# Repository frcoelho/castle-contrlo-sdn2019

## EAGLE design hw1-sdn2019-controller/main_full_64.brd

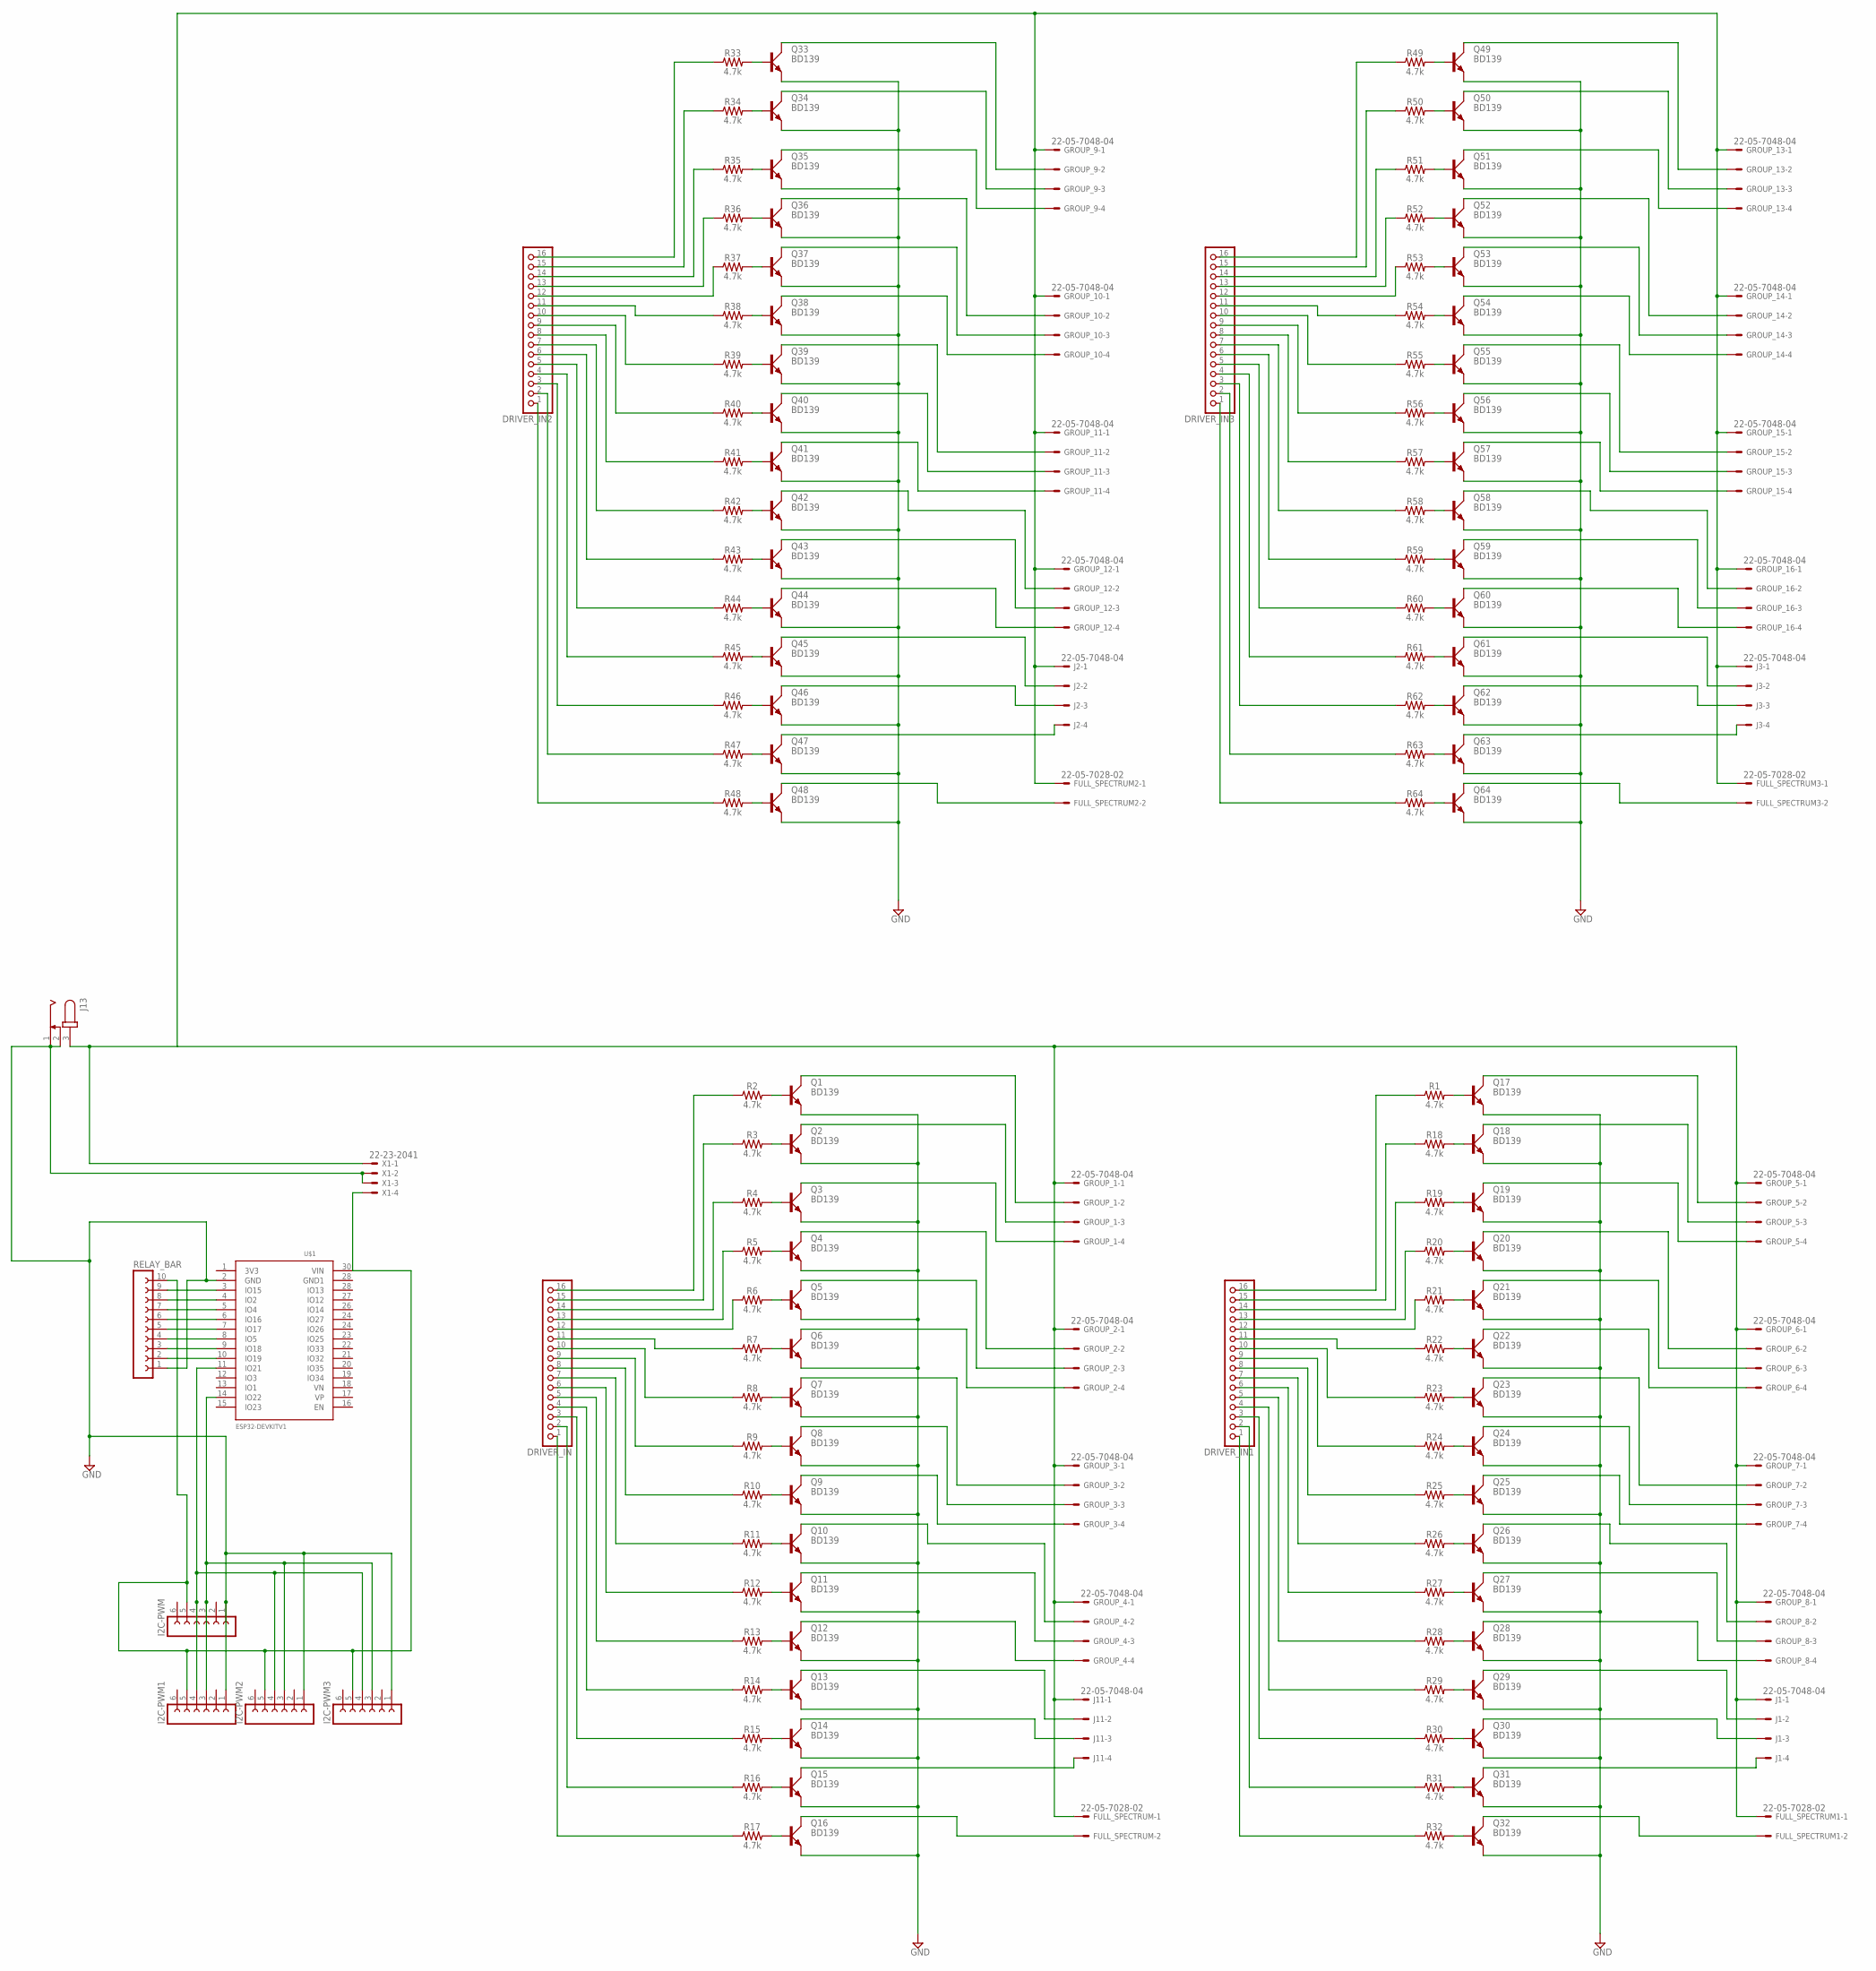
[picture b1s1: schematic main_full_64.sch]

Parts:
DRIVER_IN, DRIVER_IN1, DRIVER_IN2, DRIVER_IN3: PINHD-1X16/90; 1X16/90
FULL_SPECTRUM, FULL_SPECTRUM1, FULL_SPECTRUM2, FULL_SPECTRUM3: 22-05-7028-02; 7395-02
GROUP_1, GROUP_2, GROUP_3, GROUP_4, GROUP_5, GROUP_6, GROUP_7, GROUP_8, GROUP_9, GROUP_10, GROUP_11, GROUP_12, GROUP_13, GROUP_14, GROUP_15, GROUP_16: 22-05-7048-04; 7395-04
I2C-PWM, I2C-PWM1, I2C-PWM2, I2C-PWM3: FE06W
J1, J2, J3, J11: 22-05-7048-04; 7395-04
J13: JACK-PLUG0; SPC4077
Q1, Q2, Q3, Q4, Q5, Q6, Q7, Q8, Q9, Q10, Q11, Q12, Q13, Q14, Q15, Q16, Q17, Q18, Q19, Q20, Q21, Q22, Q23, Q24, Q25, Q26, Q27, Q28, Q29, Q30, Q31, Q32, Q33, Q34, Q35, Q36, Q37, Q38, Q39, Q40, Q41, Q42, Q43, Q44, Q45, Q46, Q47, Q48, Q49, Q50, Q51, Q52, Q53, Q54, Q55, Q56, Q57, Q58, Q59, Q60, Q61, Q62, Q63, Q64: BD139; TO126AV
R1, R2, R3, R4, R5, R6, R7, R8, R9, R10, R11, R12, R13, R14, R15, R16, R17, R18, R19, R20, R21, R22, R23, R24, R25, R26, R27, R28, R29, R30, R31, R32, R33, R34, R35, R36, R37, R38, R39, R40, R41, R42, R43, R44, R45, R46, R47, R48, R49, R50, R51, R52, R53, R54, R55, R56, R57, R58, R59, R60, R61, R62, R63, R64: 4.7k; 0603
RELAY_BAR: FE10W
U$1: ESP32DEVKITV1; ESP32-DEVKITV1
X1: 22-23-2041

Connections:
GND: I2C-PWM.1, I2C-PWM1.1, I2C-PWM2.1, I2C-PWM3.1, J13.1, J13.2, Q1.E, Q2.E, Q3.E, Q4.E, Q5.E, Q6.E, Q7.E, Q8.E, Q9.E, Q10.E, Q11.E, Q12.E, Q13.E, Q14.E, Q15.E, Q16.E, Q17.E, Q18.E, Q19.E, Q20.E, Q21.E, Q22.E, Q23.E, Q24.E, Q25.E, Q26.E, Q27.E, Q28.E, Q29.E, Q30.E, Q31.E, Q32.E, Q33.E, Q34.E, Q35.E, Q36.E, Q37.E, Q38.E, Q39.E, Q40.E, Q41.E, Q42.E, Q43.E, Q44.E, Q45.E, Q46.E, Q47.E, Q48.E, Q49.E, Q50.E, Q51.E, Q52.E, Q53.E, Q54.E, Q55.E, Q56.E, Q57.E, Q58.E, Q59.E, Q60.E, Q61.E, Q62.E, Q63.E, Q64.E, RELAY_BAR.1, U$1.2 (GND), X1.2, X1.3
unnamed: FULL_SPECTRUM.1, FULL_SPECTRUM1.1, FULL_SPECTRUM2.1, FULL_SPECTRUM3.1, GROUP_1.1, GROUP_2.1, GROUP_3.1, GROUP_4.1, GROUP_5.1, GROUP_6.1, GROUP_7.1, GROUP_8.1, GROUP_9.1, GROUP_10.1, GROUP_11.1, GROUP_12.1, GROUP_13.1, GROUP_14.1, GROUP_15.1, GROUP_16.1, J1.1, J2.1, J3.1, J11.1, J13.3, X1.1
unnamed: Q1.B, R2.2
unnamed: Q2.B, R3.2
unnamed: Q3.B, R4.2
unnamed: Q4.B, R5.2
unnamed: Q5.B, R6.2
unnamed: Q6.B, R7.2
unnamed: Q7.B, R8.2
unnamed: Q8.B, R9.2
unnamed: Q9.B, R10.2
unnamed: Q10.B, R11.2
unnamed: Q11.B, R12.2
unnamed: Q12.B, R13.2
unnamed: Q13.B, R14.2
unnamed: Q14.B, R15.2
unnamed: Q15.B, R16.2
unnamed: Q16.B, R17.2
unnamed: DRIVER_IN.1, R17.1
unnamed: DRIVER_IN.2, R16.1
unnamed: DRIVER_IN.3, R15.1
unnamed: DRIVER_IN.4, R14.1
unnamed: DRIVER_IN.5, R13.1
unnamed: DRIVER_IN.6, R12.1
unnamed: DRIVER_IN.7, R11.1
unnamed: DRIVER_IN.8, R10.1
unnamed: DRIVER_IN.9, R9.1
unnamed: DRIVER_IN.10, R8.1
unnamed: DRIVER_IN.11, R7.1
unnamed: DRIVER_IN.12, R6.1
unnamed: DRIVER_IN.13, R5.1
unnamed: DRIVER_IN.14, R4.1
unnamed: DRIVER_IN.15, R3.1
unnamed: DRIVER_IN.16, R2.1
unnamed: RELAY_BAR.9, U$1.3 (IO15)
unnamed: RELAY_BAR.8, U$1.4 (IO2)
unnamed: RELAY_BAR.7, U$1.5 (IO4)
unnamed: RELAY_BAR.6, U$1.6 (IO16)
unnamed: RELAY_BAR.5, U$1.7 (IO17)
unnamed: RELAY_BAR.4, U$1.8 (IO5)
unnamed: RELAY_BAR.3, U$1.9 (IO18)
unnamed: RELAY_BAR.2, U$1.10 (IO19)
unnamed: Q17.B, R1.2
unnamed: Q18.B, R18.2
unnamed: Q19.B, R19.2
unnamed: Q20.B, R20.2
unnamed: Q21.B, R21.2
unnamed: GROUP_1.2, Q1.C
unnamed: GROUP_1.3, Q2.C
unnamed: GROUP_1.4, Q3.C
unnamed: GROUP_2.2, Q4.C
unnamed: GROUP_2.3, Q5.C
unnamed: GROUP_2.4, Q6.C
unnamed: GROUP_3.2, Q7.C
unnamed: GROUP_3.3, Q8.C
unnamed: GROUP_3.4, Q9.C
unnamed: GROUP_4.2, Q10.C
unnamed: GROUP_4.3, Q11.C
unnamed: GROUP_4.4, Q12.C
unnamed: Q22.B, R22.2
unnamed: J11.2, Q13.C
unnamed: J11.3, Q14.C
unnamed: J11.4, Q15.C
unnamed: FULL_SPECTRUM.2, Q16.C
unnamed: Q23.B, R23.2
unnamed: Q24.B, R24.2
unnamed: Q25.B, R25.2
unnamed: Q26.B, R26.2
unnamed: Q27.B, R27.2
unnamed: Q28.B, R28.2
unnamed: Q29.B, R29.2
unnamed: Q30.B, R30.2
unnamed: Q31.B, R31.2
unnamed: Q32.B, R32.2
unnamed: DRIVER_IN1.1, R32.1
unnamed: DRIVER_IN1.2, R31.1
unnamed: DRIVER_IN1.3, R30.1
unnamed: DRIVER_IN1.4, R29.1
unnamed: DRIVER_IN1.5, R28.1
unnamed: DRIVER_IN1.6, R27.1
unnamed: DRIVER_IN1.7, R26.1
unnamed: DRIVER_IN1.8, R25.1
unnamed: DRIVER_IN1.9, R24.1
unnamed: DRIVER_IN1.10, R23.1
unnamed: DRIVER_IN1.11, R22.1
unnamed: DRIVER_IN1.12, R21.1
unnamed: DRIVER_IN1.13, R20.1
unnamed: DRIVER_IN1.14, R19.1
unnamed: DRIVER_IN1.15, R18.1
unnamed: DRIVER_IN1.16, R1.1
unnamed: GROUP_5.2, Q17.C
unnamed: GROUP_5.3, Q18.C
unnamed: GROUP_5.4, Q19.C
unnamed: GROUP_6.2, Q20.C
unnamed: GROUP_6.3, Q21.C
unnamed: GROUP_6.4, Q22.C
unnamed: GROUP_7.2, Q23.C
unnamed: GROUP_7.3, Q24.C
unnamed: GROUP_7.4, Q25.C
unnamed: GROUP_8.2, Q26.C
unnamed: GROUP_8.3, Q27.C
unnamed: GROUP_8.4, Q28.C
unnamed: J1.2, Q29.C
unnamed: J1.3, Q30.C
unnamed: J1.4, Q31.C
unnamed: FULL_SPECTRUM1.2, Q32.C
unnamed: Q33.B, R33.2
unnamed: Q34.B, R34.2
unnamed: Q35.B, R35.2
unnamed: Q36.B, R36.2
unnamed: Q37.B, R37.2
unnamed: Q38.B, R38.2
unnamed: Q39.B, R39.2
unnamed: Q40.B, R40.2
unnamed: Q41.B, R41.2
unnamed: Q42.B, R42.2
unnamed: Q43.B, R43.2
unnamed: Q44.B, R44.2
unnamed: Q45.B, R45.2
unnamed: Q46.B, R46.2
unnamed: Q47.B, R47.2
unnamed: Q48.B, R48.2
unnamed: DRIVER_IN2.1, R48.1
unnamed: DRIVER_IN2.2, R47.1
unnamed: DRIVER_IN2.3, R46.1
unnamed: DRIVER_IN2.4, R45.1
unnamed: DRIVER_IN2.5, R44.1
unnamed: DRIVER_IN2.6, R43.1
unnamed: DRIVER_IN2.7, R42.1
unnamed: DRIVER_IN2.8, R41.1
unnamed: DRIVER_IN2.9, R40.1
unnamed: DRIVER_IN2.10, R39.1
unnamed: DRIVER_IN2.11, R38.1
unnamed: DRIVER_IN2.12, R37.1
unnamed: DRIVER_IN2.13, R36.1
unnamed: DRIVER_IN2.14, R35.1
unnamed: DRIVER_IN2.15, R34.1
unnamed: DRIVER_IN2.16, R33.1
unnamed: GROUP_9.2, Q33.C
unnamed: GROUP_9.3, Q34.C
unnamed: GROUP_9.4, Q35.C
unnamed: GROUP_10.2, Q36.C
unnamed: GROUP_10.3, Q37.C
unnamed: GROUP_10.4, Q38.C
unnamed: GROUP_11.2, Q39.C
unnamed: GROUP_11.3, Q40.C
unnamed: GROUP_11.4, Q41.C
unnamed: GROUP_12.2, Q42.C
unnamed: GROUP_12.3, Q43.C
unnamed: GROUP_12.4, Q44.C
unnamed: J2.2, Q45.C
unnamed: J2.3, Q46.C
unnamed: J2.4, Q47.C
unnamed: FULL_SPECTRUM2.2, Q48.C
unnamed: Q49.B, R49.2
unnamed: Q50.B, R50.2
unnamed: Q51.B, R51.2
unnamed: Q52.B, R52.2
unnamed: Q53.B, R53.2
unnamed: Q54.B, R54.2
unnamed: Q55.B, R55.2
unnamed: Q56.B, R56.2
unnamed: Q57.B, R57.2
unnamed: Q58.B, R58.2
unnamed: Q59.B, R59.2
unnamed: Q60.B, R60.2
unnamed: Q61.B, R61.2
unnamed: Q62.B, R62.2
unnamed: Q63.B, R63.2
unnamed: Q64.B, R64.2
unnamed: DRIVER_IN3.1, R64.1
unnamed: DRIVER_IN3.2, R63.1
unnamed: DRIVER_IN3.3, R62.1
unnamed: DRIVER_IN3.4, R61.1
unnamed: DRIVER_IN3.5, R60.1
unnamed: DRIVER_IN3.6, R59.1
unnamed: DRIVER_IN3.7, R58.1
unnamed: DRIVER_IN3.8, R57.1
unnamed: DRIVER_IN3.9, R56.1
unnamed: DRIVER_IN3.10, R55.1
unnamed: DRIVER_IN3.11, R54.1
unnamed: DRIVER_IN3.12, R53.1
unnamed: DRIVER_IN3.13, R52.1
unnamed: DRIVER_IN3.14, R51.1
unnamed: DRIVER_IN3.15, R50.1
unnamed: DRIVER_IN3.16, R49.1
unnamed: GROUP_13.2, Q49.C
unnamed: GROUP_13.3, Q50.C
unnamed: GROUP_13.4, Q51.C
unnamed: GROUP_14.2, Q52.C
unnamed: GROUP_14.3, Q53.C
unnamed: GROUP_14.4, Q54.C
unnamed: GROUP_15.2, Q55.C
unnamed: GROUP_15.3, Q56.C
unnamed: GROUP_15.4, Q57.C
unnamed: GROUP_16.2, Q58.C
unnamed: GROUP_16.3, Q59.C
unnamed: GROUP_16.4, Q60.C
unnamed: J3.2, Q61.C
unnamed: J3.3, Q62.C
unnamed: J3.4, Q63.C
unnamed: FULL_SPECTRUM3.2, Q64.C
unnamed: I2C-PWM.4, I2C-PWM1.4, I2C-PWM2.4, I2C-PWM3.4, U$1.11 (IO21)
unnamed: I2C-PWM.3, I2C-PWM1.3, I2C-PWM2.3, I2C-PWM3.3, U$1.14 (IO22)
unnamed: I2C-PWM.5, I2C-PWM1.5, I2C-PWM2.5, I2C-PWM3.5, RELAY_BAR.10, U$1.30 (VIN), X1.4

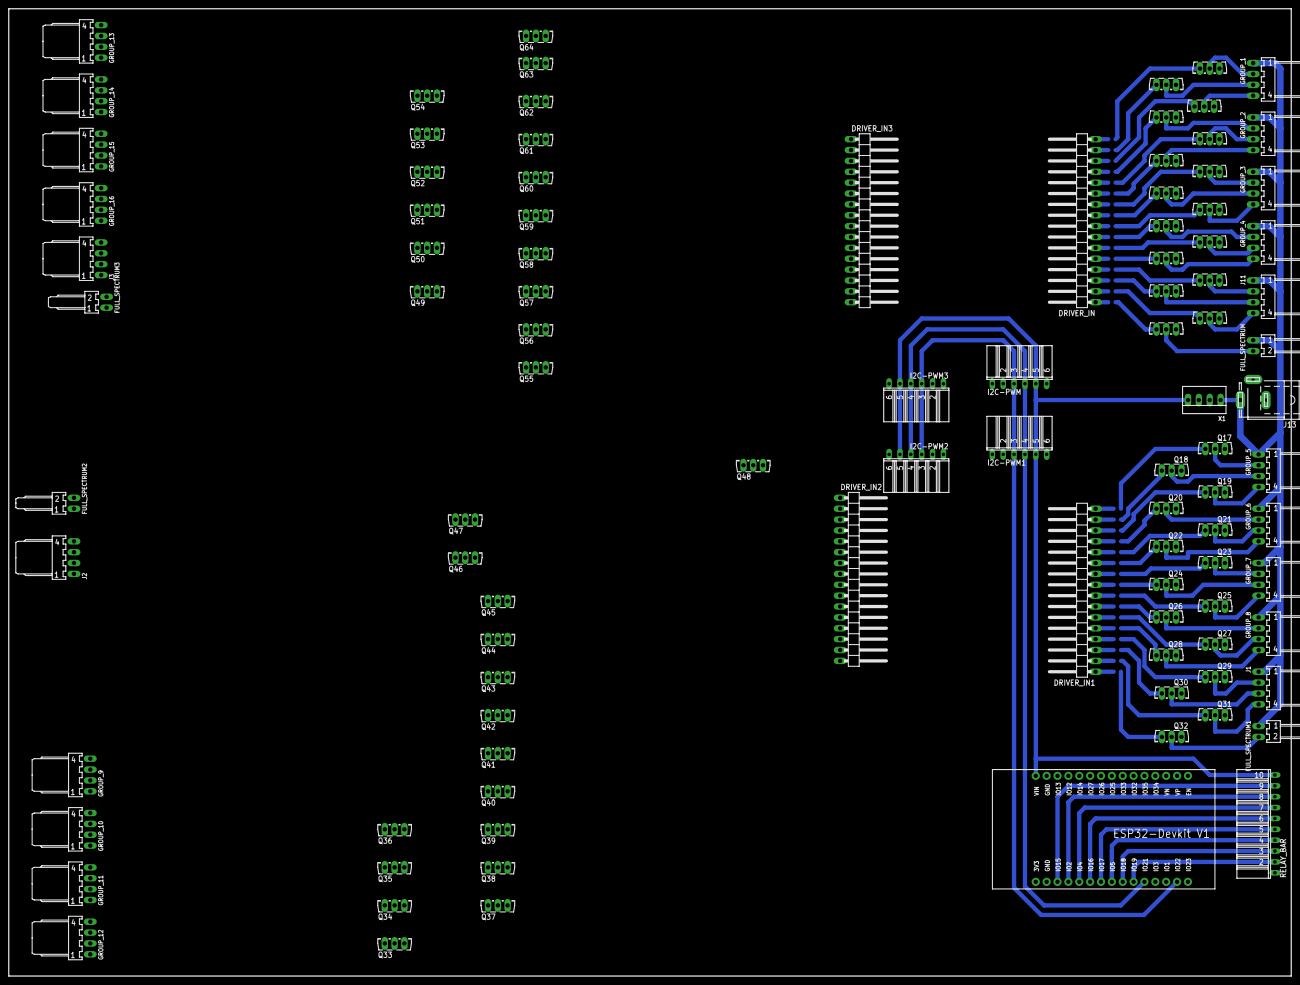
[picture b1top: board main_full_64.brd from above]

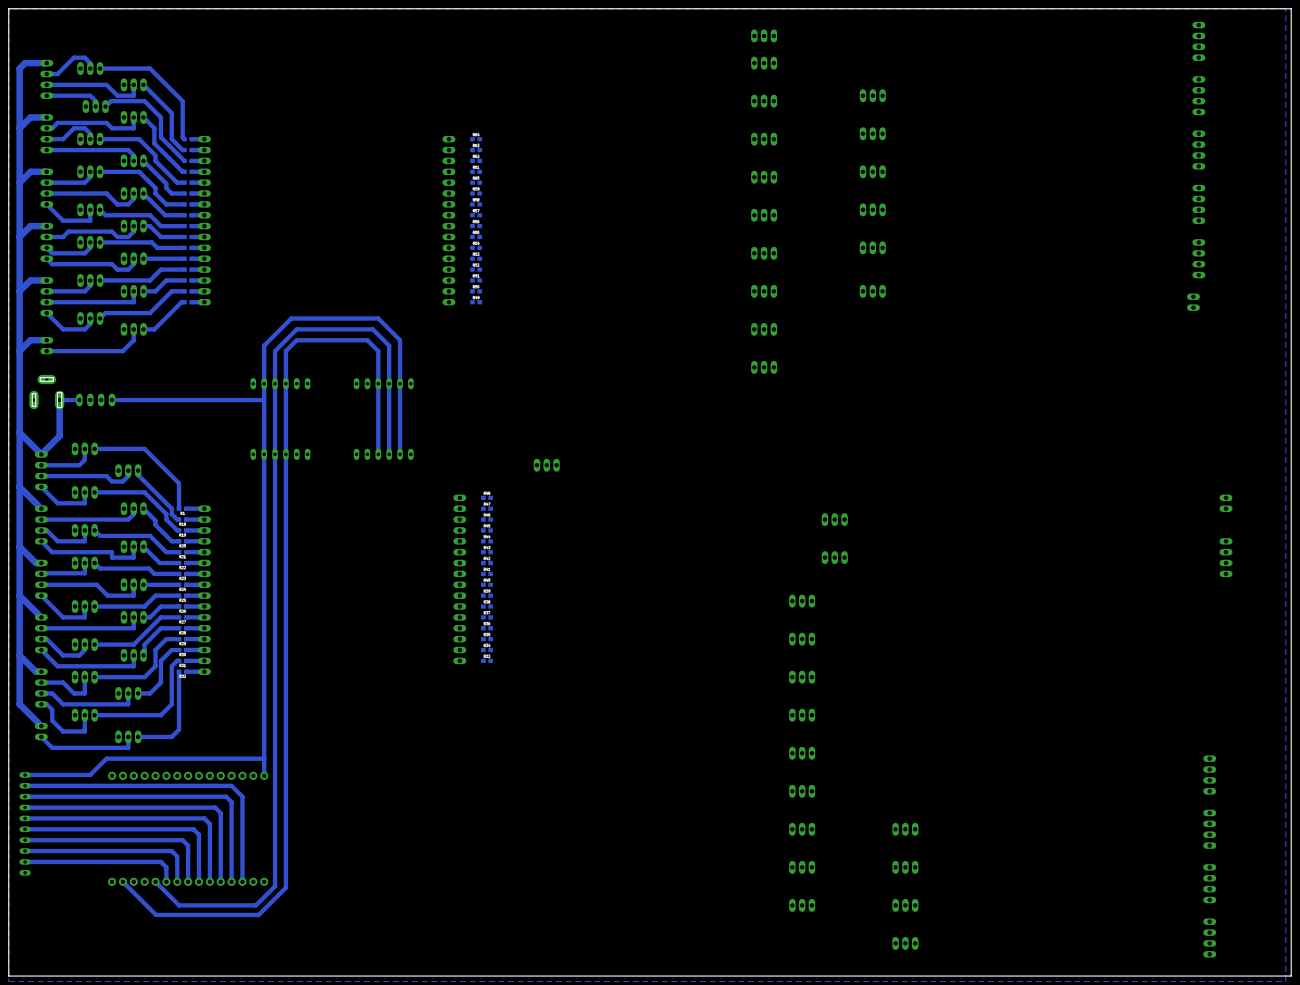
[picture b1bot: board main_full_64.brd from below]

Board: 2 copper layers, 299.7 x 226.1 mm, 164 parts (64 on the bottom side), 205 nets.

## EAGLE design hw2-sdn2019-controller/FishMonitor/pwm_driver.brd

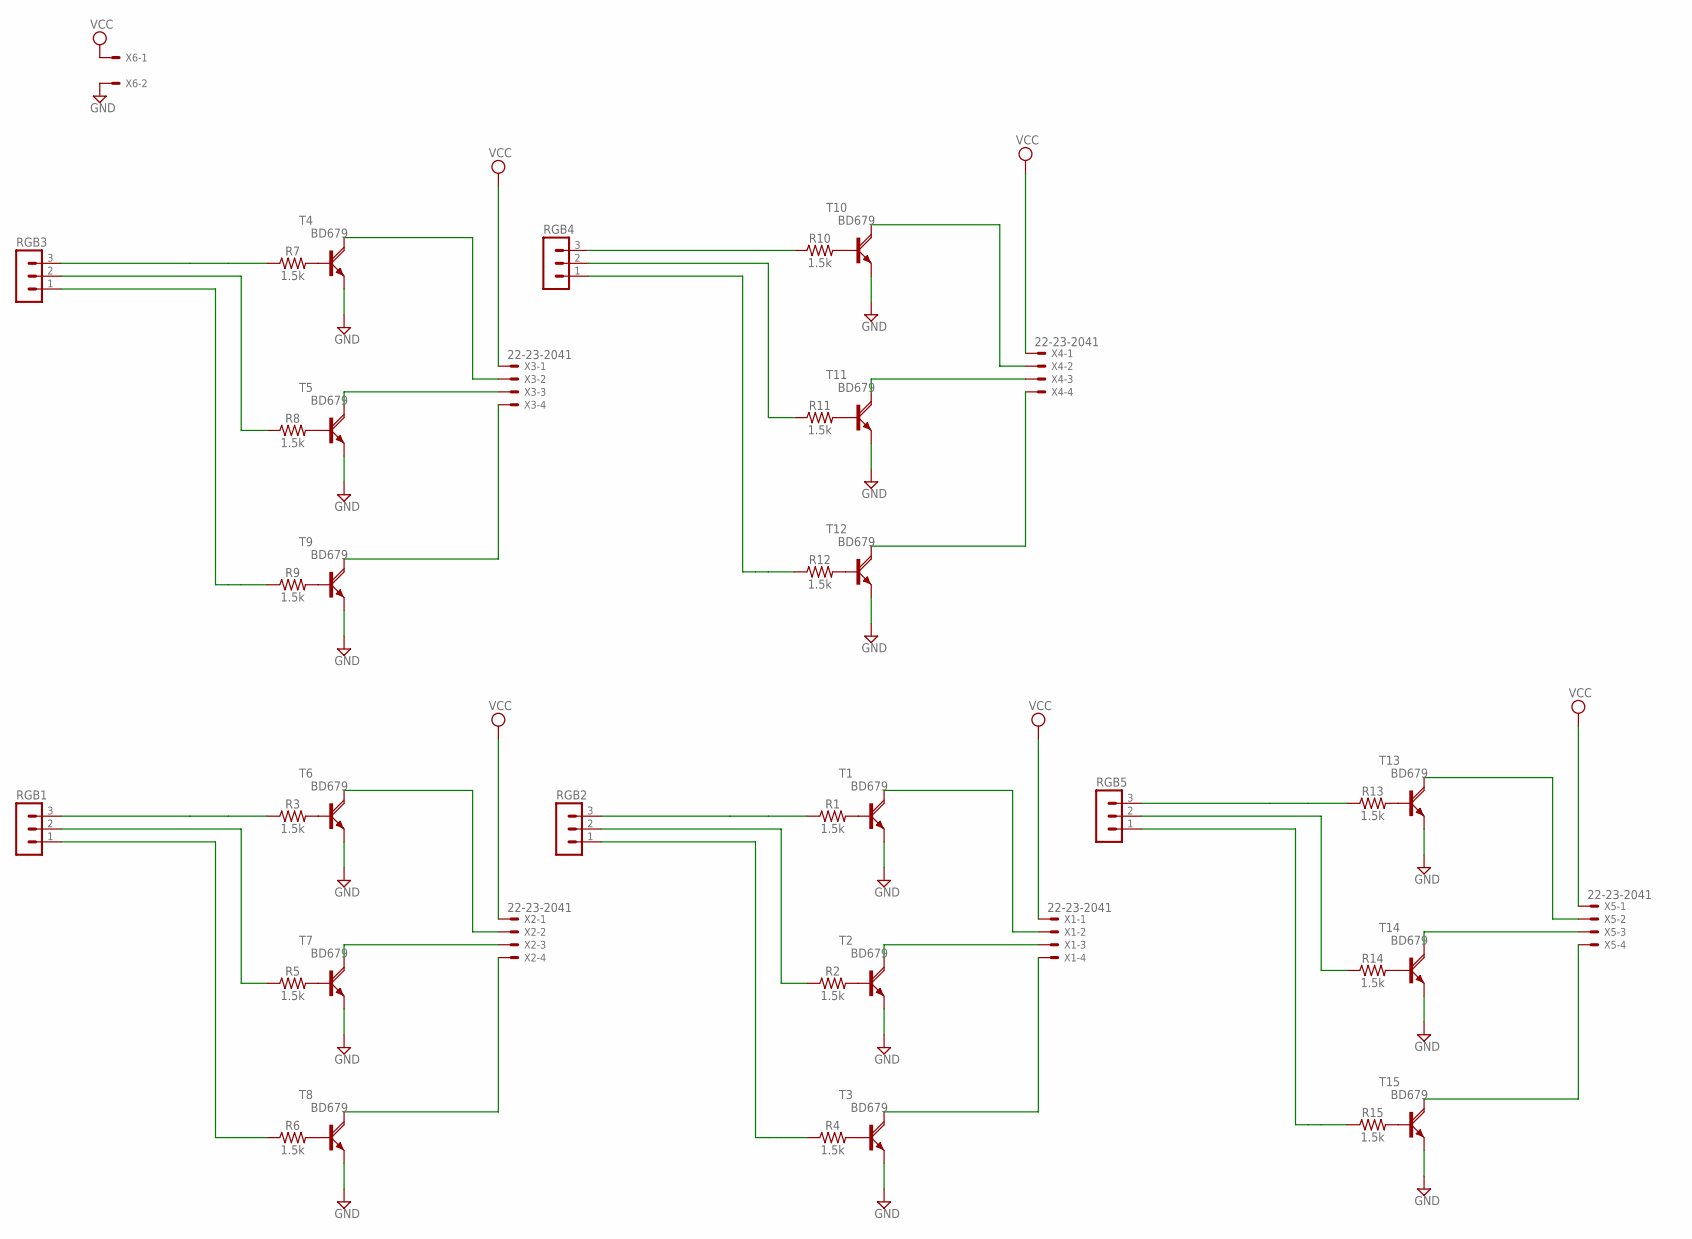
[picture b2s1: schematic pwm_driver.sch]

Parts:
R1, R2, R3, R4, R5, R6, R7, R8, R9, R10, R11, R12, R13, R14, R15: 1.5k; 0603
RGB1, RGB2, RGB3, RGB4, RGB5: MA03-1
T1, T2, T3, T4, T5, T6, T7, T8, T9, T10, T11, T12, T13, T14, T15: BD679; TO126AV
X1, X2, X3, X4, X5: 22-23-2041
X6: KK-156-2

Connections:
GND: T1.E, T2.E, T3.E, T4.E, T5.E, T6.E, T7.E, T8.E, T9.E, T10.E, T11.E, T12.E, T13.E, T14.E, T15.E, X6.2
unnamed: R3.2, T6.B
unnamed: R5.2, T7.B
unnamed: R6.2, T8.B
unnamed: R1.1, RGB2.3
unnamed: R2.1, RGB2.2
unnamed: R4.1, RGB2.1
unnamed: T1.C, X1.2
unnamed: T2.C, X1.3
unnamed: T3.C, X1.4
unnamed: R1.2, T1.B
unnamed: R2.2, T2.B
unnamed: R4.2, T3.B
unnamed: R7.1, RGB3.3
unnamed: R8.1, RGB3.2
unnamed: R9.1, RGB3.1
unnamed: R3.1, RGB1.3
unnamed: R5.1, RGB1.2
unnamed: R6.1, RGB1.1
unnamed: T4.C, X3.2
unnamed: T5.C, X3.3
unnamed: T6.C, X2.2
unnamed: T7.C, X2.3
unnamed: T8.C, X2.4
unnamed: T9.C, X3.4
unnamed: R7.2, T4.B
unnamed: R8.2, T5.B
unnamed: R9.2, T9.B
unnamed: R10.1, RGB4.3
unnamed: R11.1, RGB4.2
unnamed: R12.1, RGB4.1
unnamed: T10.C, X4.2
unnamed: T11.C, X4.3
unnamed: T12.C, X4.4
unnamed: R10.2, T10.B
unnamed: R11.2, T11.B
unnamed: R12.2, T12.B
unnamed: R13.1, RGB5.3
unnamed: R14.1, RGB5.2
unnamed: R15.1, RGB5.1
unnamed: T13.C, X5.2
unnamed: T14.C, X5.3
unnamed: T15.C, X5.4
unnamed: R13.2, T13.B
unnamed: R14.2, T14.B
unnamed: R15.2, T15.B
VCC: X1.1, X2.1, X3.1, X4.1, X5.1, X6.1

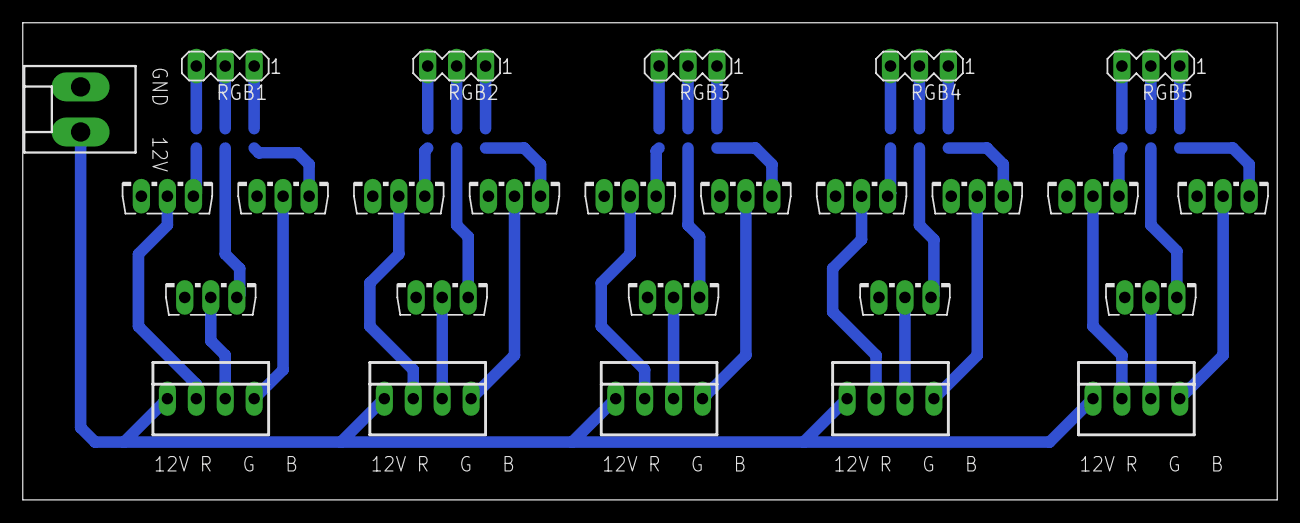
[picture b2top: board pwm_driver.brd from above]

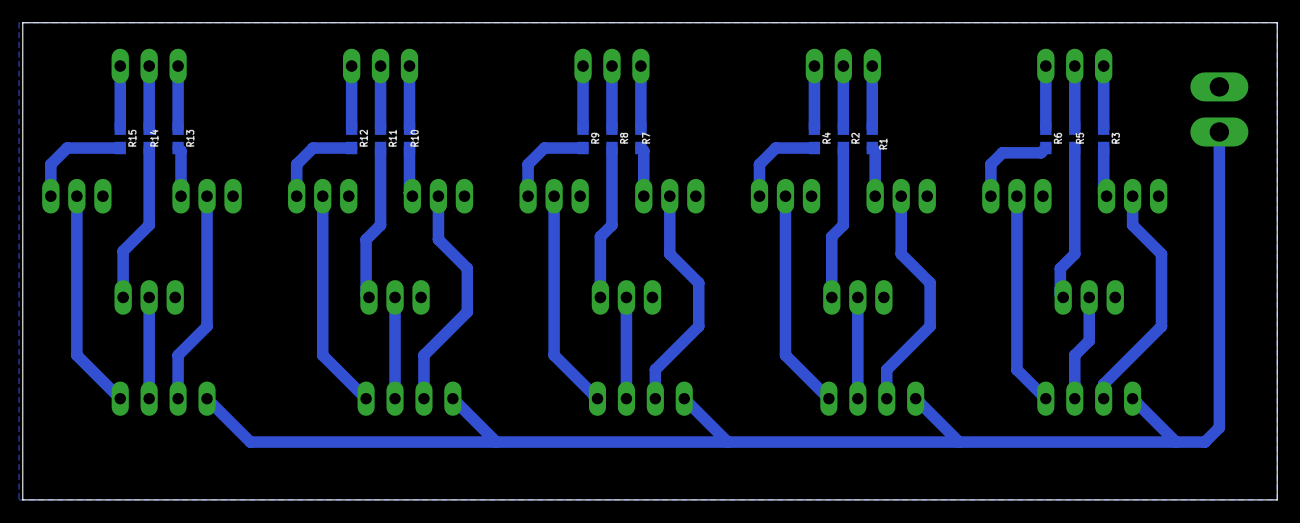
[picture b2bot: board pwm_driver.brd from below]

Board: 2 copper layers, 110.2 x 41.9 mm, 41 parts (15 on the bottom side), 47 nets.

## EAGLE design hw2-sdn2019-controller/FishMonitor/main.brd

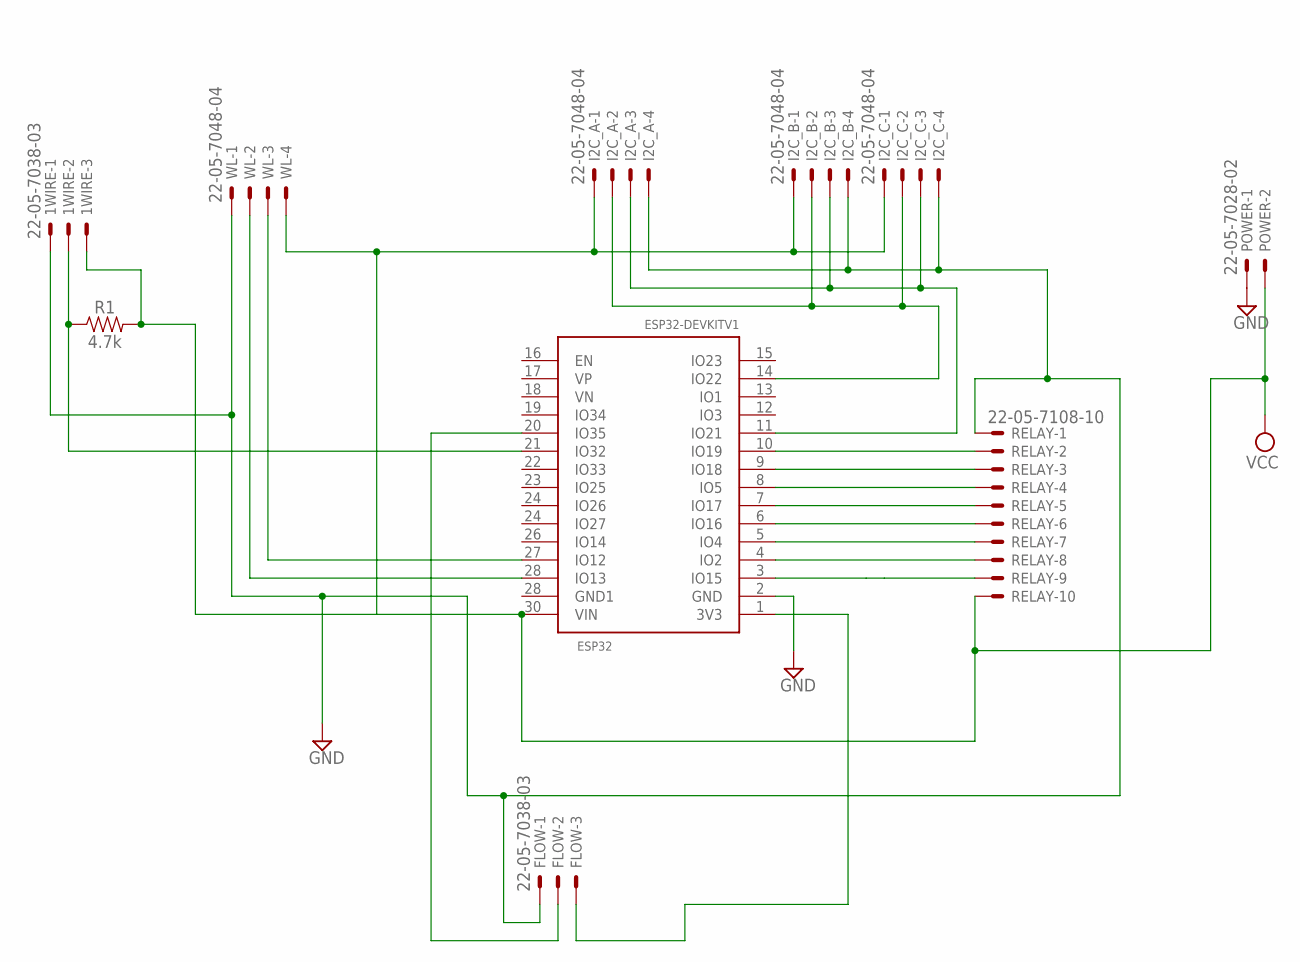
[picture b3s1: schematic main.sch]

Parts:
1WIRE: 22-05-7038-03; 7395-03
ESP32: ESP32DEVKITV1; ESP32-DEVKITV1
FLOW: 22-05-7038-03; 7395-03
I2C_A, I2C_B, I2C_C: 22-05-7048-04; 7395-04
POWER: 22-05-7028-02; 7395-02
R1: 4.7k; 0603
RELAY: 22-05-7108-10; 7395-10
WL: 22-05-7048-04; 7395-04

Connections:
GND: 1WIRE.1, ESP32.2 (GND), FLOW.1, I2C_A.4, I2C_B.4, I2C_C.4, POWER.1, RELAY.1, WL.1
unnamed: ESP32.3 (IO15), RELAY.9
unnamed: ESP32.4 (IO2), RELAY.8
unnamed: ESP32.5 (IO4), RELAY.7
unnamed: ESP32.6 (IO16), RELAY.6
unnamed: ESP32.7 (IO17), RELAY.5
unnamed: ESP32.8 (IO5), RELAY.4
unnamed: ESP32.9 (IO18), RELAY.3
unnamed: ESP32.10 (IO19), RELAY.2
unnamed: ESP32.27 (IO12), WL.3
unnamed: ESP32.28 (IO13), WL.2
unnamed: ESP32.11 (IO21), I2C_A.3, I2C_B.3, I2C_C.3
unnamed: ESP32.14 (IO22), I2C_A.2, I2C_B.2, I2C_C.2
unnamed: 1WIRE.2, ESP32.21 (IO32), R1.1
unnamed: ESP32.20 (IO35), FLOW.2
unnamed: ESP32.1 (3V3), FLOW.3
VCC: 1WIRE.3, ESP32.30 (VIN), I2C_A.1, I2C_B.1, I2C_C.1, POWER.2, R1.2, RELAY.10, WL.4

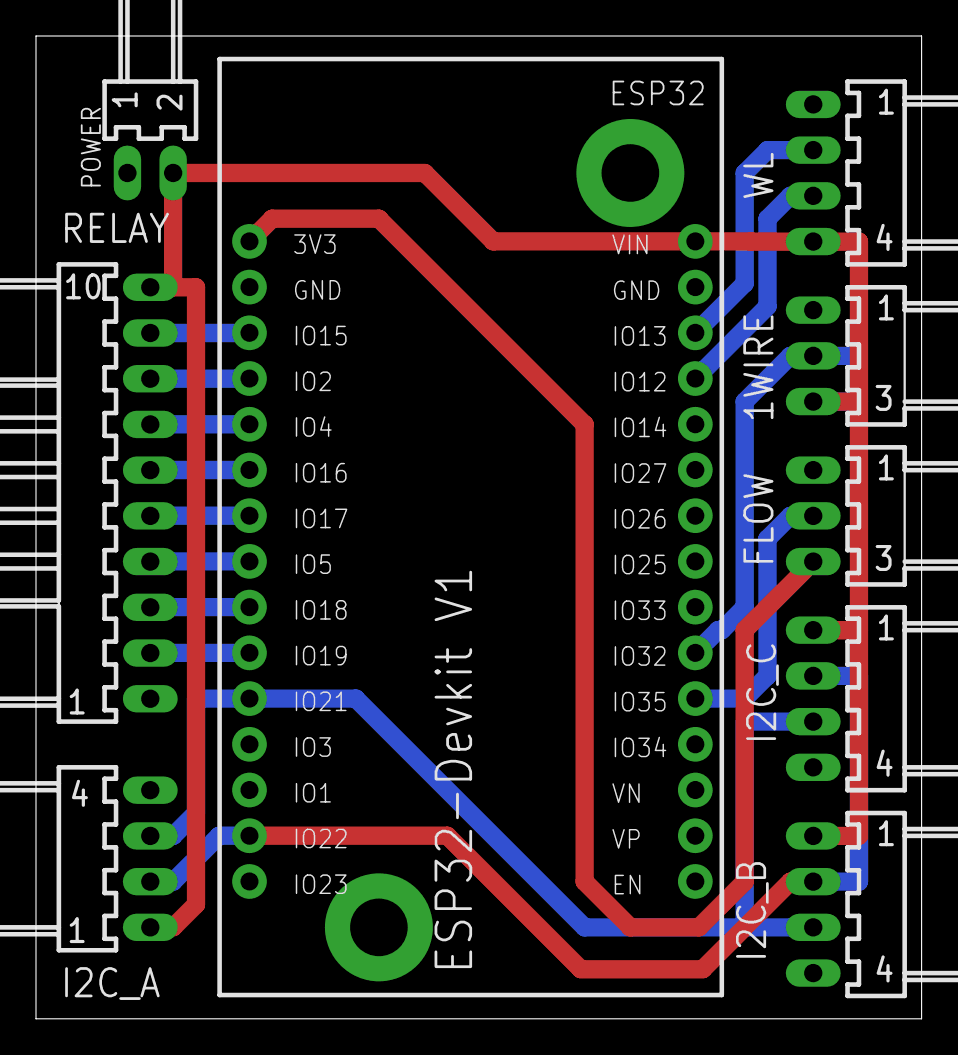
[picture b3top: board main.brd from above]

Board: 2 copper layers, 49.2 x 54.6 mm, 10 parts (1 on the bottom side), 17 nets.

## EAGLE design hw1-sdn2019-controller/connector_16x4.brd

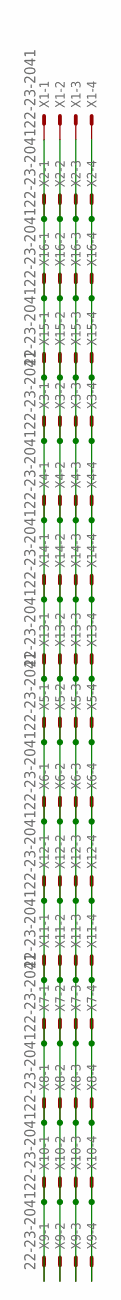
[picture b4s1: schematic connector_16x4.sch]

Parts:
X1, X2, X3, X4, X5, X6, X7, X8, X9, X10, X11, X12, X13, X14, X15, X16: 22-23-2041

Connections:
unnamed: X1.1, X2.1, X3.1, X4.1, X5.1, X6.1, X7.1, X8.1, X9.1, X10.1, X11.1, X12.1, X13.1, X14.1, X15.1, X16.1
unnamed: X1.2, X2.2, X3.2, X4.2, X5.2, X6.2, X7.2, X8.2, X9.2, X10.2, X11.2, X12.2, X13.2, X14.2, X15.2, X16.2
unnamed: X1.3, X2.3, X3.3, X4.3, X5.3, X6.3, X7.3, X8.3, X9.3, X10.3, X11.3, X12.3, X13.3, X14.3, X15.3, X16.3
unnamed: X1.4, X2.4, X3.4, X4.4, X5.4, X6.4, X7.4, X8.4, X9.4, X10.4, X11.4, X12.4, X13.4, X14.4, X15.4, X16.4

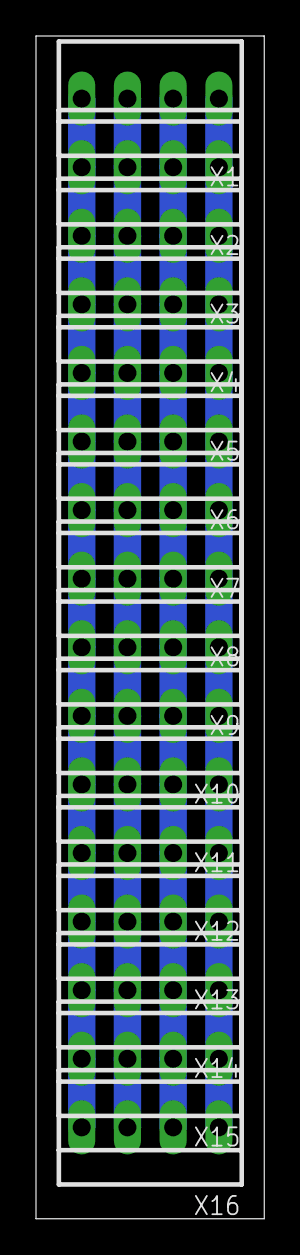
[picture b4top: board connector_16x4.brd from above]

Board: 2 copper layers, 12.7 x 65.7 mm, 16 parts (0 on the bottom side), 4 nets.

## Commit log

2022-05-26 source code thermometer-pf2020

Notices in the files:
parts and their libraries:
SparkFun-Resistors: Licensing: Creative Commons ShareAlike 4.0 International - https://creativecommons.org/licenses/by-sa/4.0
